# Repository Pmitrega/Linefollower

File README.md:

# Linefollower
Robot is made on self-designed board with attached self-designed reflective sensors using ir diode and phototransistor.
For this moment there is algorithm estimating angle error, velocity control using PI controller, and angle P controller to follow line. Succesfully tested on track.
Can be also controlled using bluetooth with xbox controller by sending ascii commands.

Project is finnished, probably won't be updated. Contiunation of LF project is under this link: [Linefollower_V2](https://github.com/Pmitrega/Linefollower_V2)

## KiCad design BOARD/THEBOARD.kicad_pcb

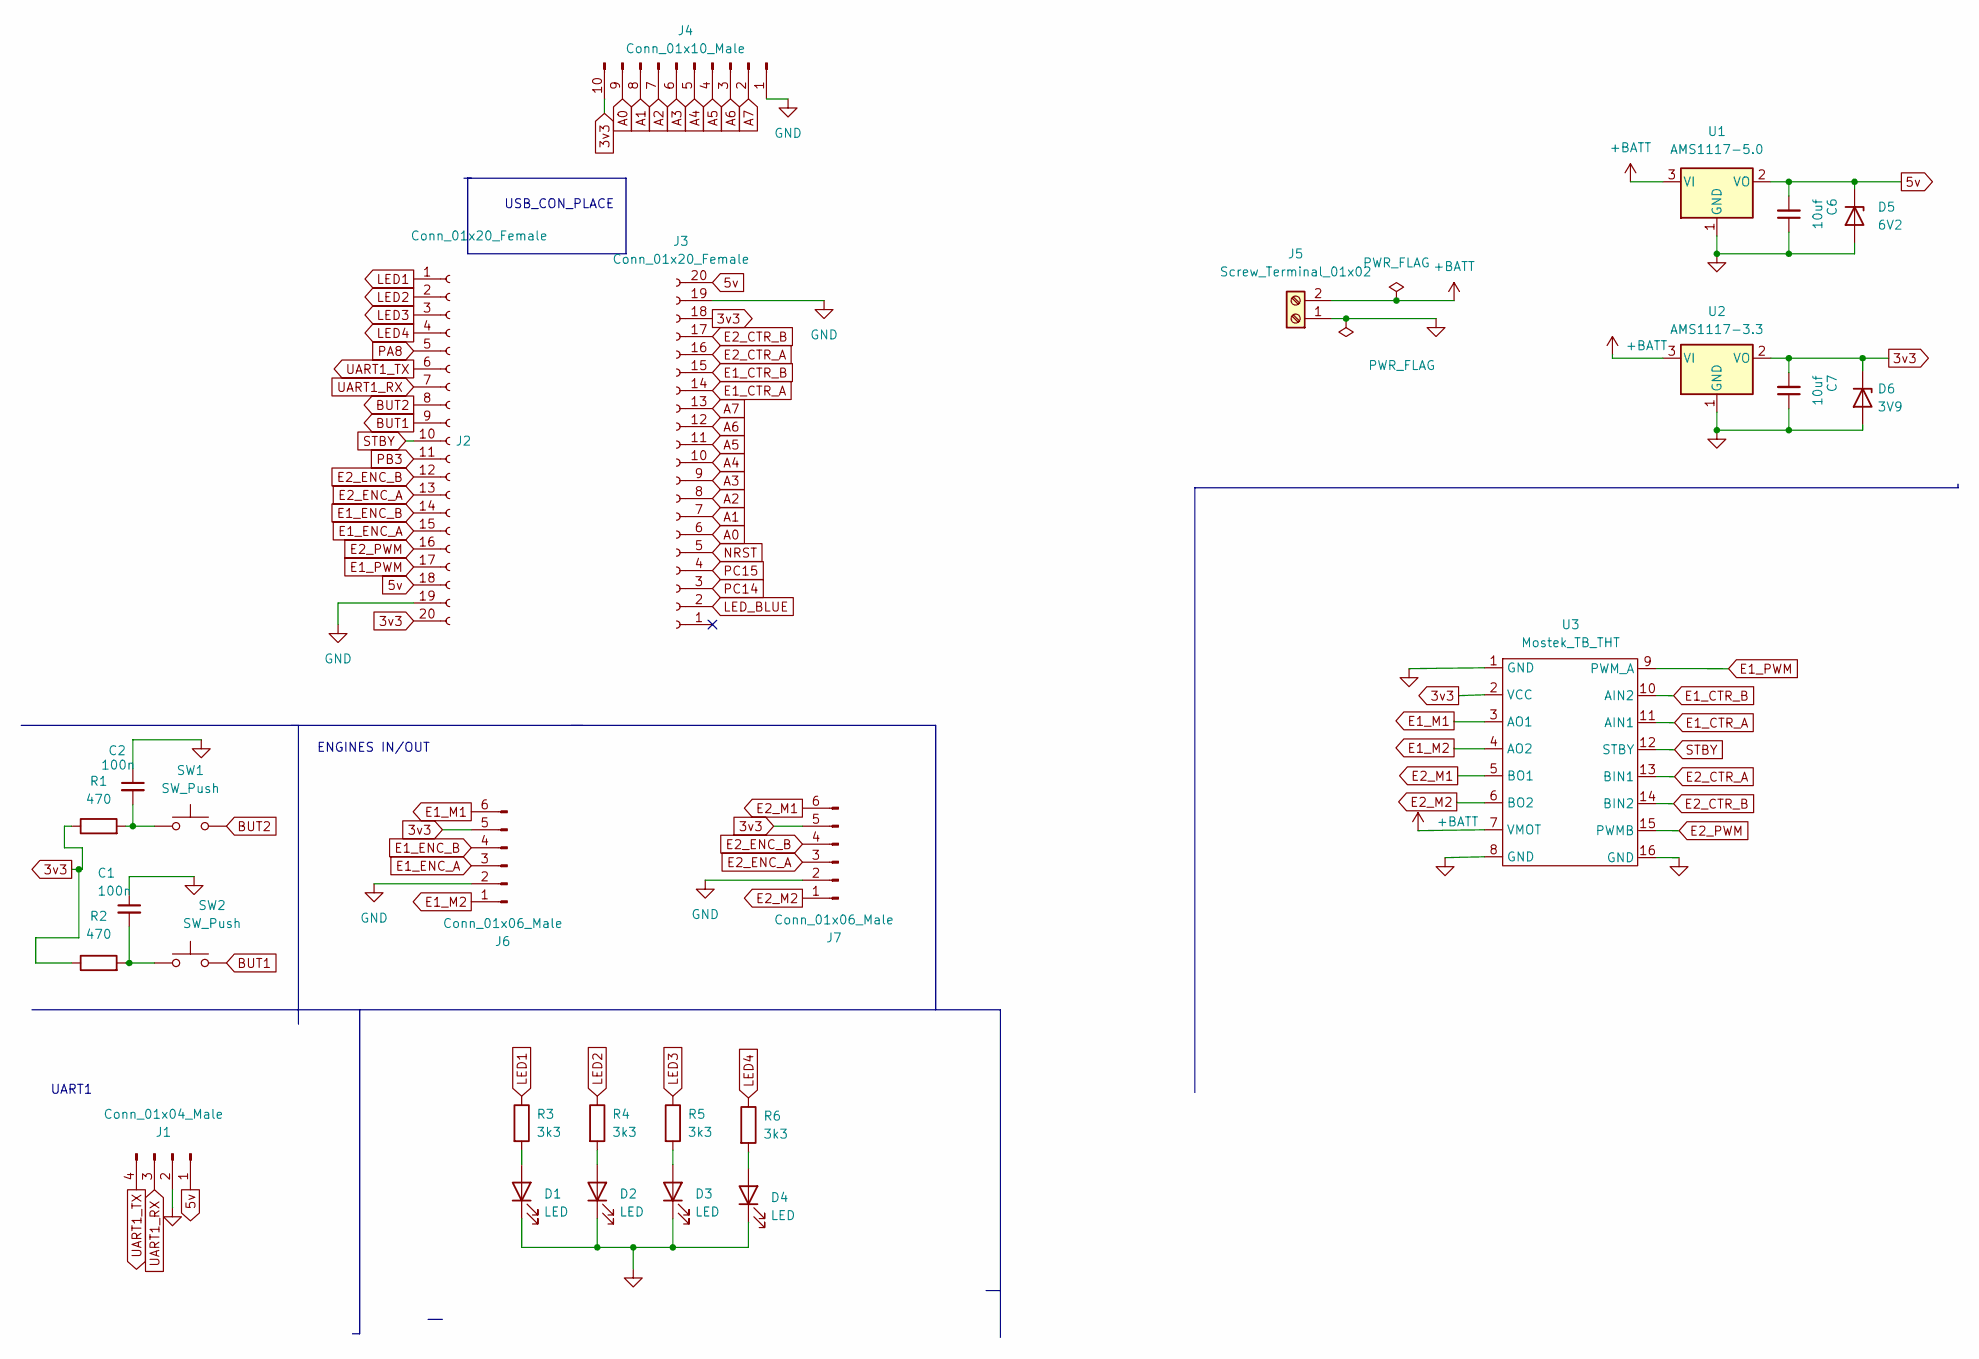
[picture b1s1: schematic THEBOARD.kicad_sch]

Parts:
C1, C2: 100n; C_0805_2012Metric_Pad1.18x1.45mm_HandSolder
C6, C7: 10uf; CP_EIA-3216-18_Kemet-A_Pad1.58x1.35mm_HandSolder
D1, D2, D3, D4: LED; D_0805_2012Metric_Pad1.15x1.40mm_HandSolder
D5: 6V2; D_MiniMELF_Handsoldering
D6: 3V9; D_MiniMELF_Handsoldering
J1: Conn_01x04_Male; PinSocket_1x04_P2.54mm_Vertical
J2, J3: Conn_01x20_Female; PinSocket_1x20_P2.54mm_Vertical
J4: Conn_01x10_Male; PinSocket_1x10_P2.54mm_Vertical
J5: Screw_Terminal_01x02; TerminalBlock_Altech_AK300-2_P5.00mm
J6, J7: Conn_01x06_Male; PinSocket_1x06_P2.54mm_Vertical
R1, R2: 470; R_0805_2012Metric_Pad1.20x1.40mm_HandSolder
R3, R4, R5, R6: 3k3; R_0805_2012Metric_Pad1.20x1.40mm_HandSolder
SW1, SW2: SW_Push; SW_PUSH_6mm
U1: AMS1117-5.0; SOT-223-3_TabPin2
U2: AMS1117-3.3; SOT-223-3_TabPin2
U3: Mostek_TB_THT; H_BRIDGE

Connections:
3v3: C7.2, D6.1 (K), J2.20, J3.18, J4.10, J6.5, J7.5, R1.1, R2.1, U2.2 (VO), U3.2 (VCC)
5v: C6.2, D5.1 (K), J1.1, J2.18, J3.20, U1.2 (VO)
+BATT: J5.2, U1.3 (VI), U2.3 (VI), U3.7 (VMOT); also elsewhere on the board
A0: J3.6, J4.9
A1: J3.7, J4.8
A2: J3.8, J4.7
A3: J3.9, J4.6
A4: J3.10, J4.5
A5: J3.11, J4.4
A6: J3.12, J4.3
A7: J3.13, J4.2
BUT1: J2.9, SW2.2
BUT2: J2.8, SW1.2
E1_CTR_A: J3.14, U3.11 (AIN1)
E1_CTR_B: J3.15, U3.10 (AIN2)
E1_ENC_A: J2.15, J6.3
E1_ENC_B: J2.14, J6.4
E1_M1: J6.6, U3.3 (AO1)
E1_M2: J6.1, U3.4 (AO2)
E1_PWM: J2.17, U3.9 (PWM_A)
E2_CTR_A: J3.16, U3.13 (BIN1)
E2_CTR_B: J3.17, U3.14 (BIN2)
E2_ENC_A: J2.13, J7.3
E2_ENC_B: J2.12, J7.4
E2_M1: J7.6, U3.5 (BO1)
E2_M2: J7.1, U3.6 (BO2)
E2_PWM: J2.16, U3.15 (PWMB)
GND: C1.1, C2.1, C6.1, C7.1, D1.1 (K), D2.1 (K), D3.1 (K), D4.1 (K), D5.2 (A), D6.2 (A), J1.2, J2.19, J3.19, J4.1, J5.1, J6.2, J7.2, U1.1 (GND), U2.1 (GND), U3.1 (GND), U3.8 (GND), U3.16 (GND); also elsewhere on the board
LED1: J2.1, R3.1
LED2: J2.2, R4.1
LED3: J2.3, R5.1
LED4: J2.4, R6.1
LED_BLUE: J3.2
NRST: J3.5
unnamed: C1.2, R2.2, SW2.1
unnamed: C2.2, R1.2, SW1.1
unnamed: D1.2 (A), R3.2
unnamed: D2.2 (A), R4.2
unnamed: D3.2 (A), R5.2
unnamed: D4.2 (A), R6.2
PA8: J2.5
PB3: J2.11
PC14: J3.3
PC15: J3.4
STBY: J2.10, U3.12 (STBY)
UART1_RX: J1.3, J2.7
UART1_TX: J1.4, J2.6

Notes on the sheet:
UART1
USB_CON_PLACE
ENGINES IN/OUT

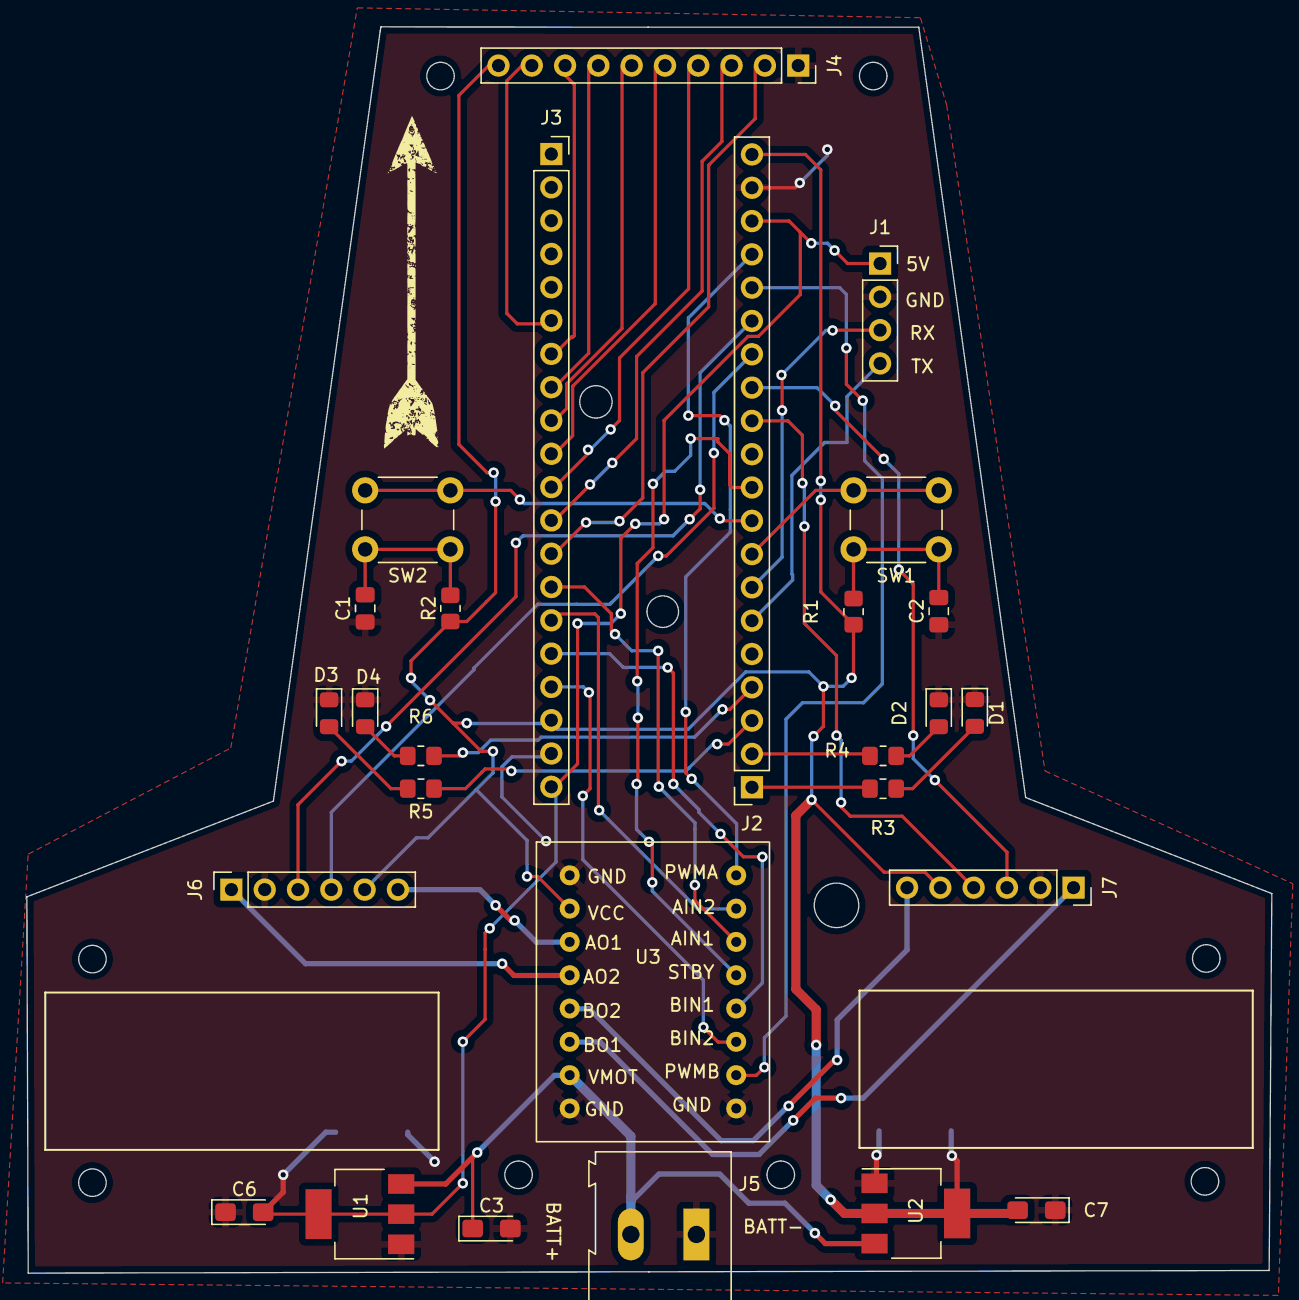
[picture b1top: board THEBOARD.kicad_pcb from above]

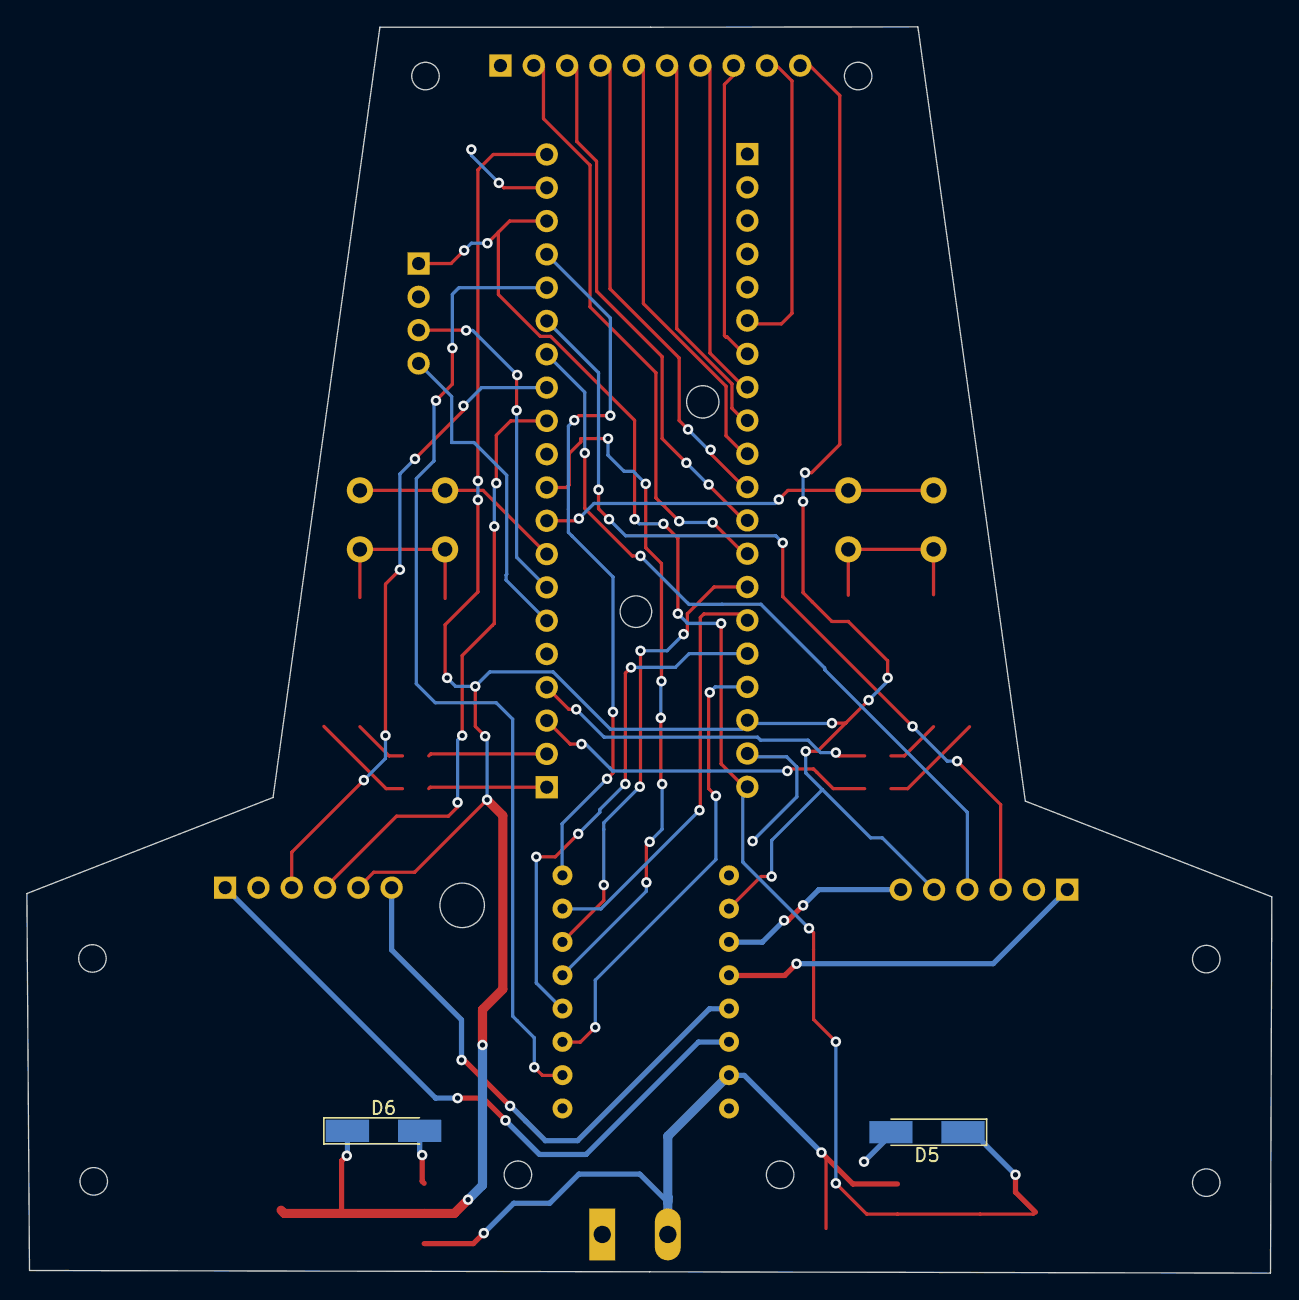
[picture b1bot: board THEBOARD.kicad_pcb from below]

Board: 2 copper layers, 95.0 x 95.0 mm, 29 parts (2 on the bottom side), 41 nets.

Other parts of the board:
C3: 10uf; CP_EIA-3216-18_Kemet-A_Pad1.58x1.35mm_HandSolder

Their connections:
+BATT: C3.1; also elsewhere on the board
GND: C3.2; also elsewhere on the board

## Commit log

2022-12-18 Added PWM control of engines and encoder readings
2022-12-21 motors pid
2022-12-21 motor PID
2022-12-21 Follows line - P controller, simple angle estimation
2022-12-21 Better controller, going much faster, fixed out of range angle estimation (keeps last value, when there is no sensor detection)
2022-12-21 added video and images
2022-12-21 changed video to gif
2023-01-01 board schematics
2023-01-19 added blutooth wireless controll + app for xbox controller ( can be moved by joystick and automatic controll can be turend on/off pressing A)
